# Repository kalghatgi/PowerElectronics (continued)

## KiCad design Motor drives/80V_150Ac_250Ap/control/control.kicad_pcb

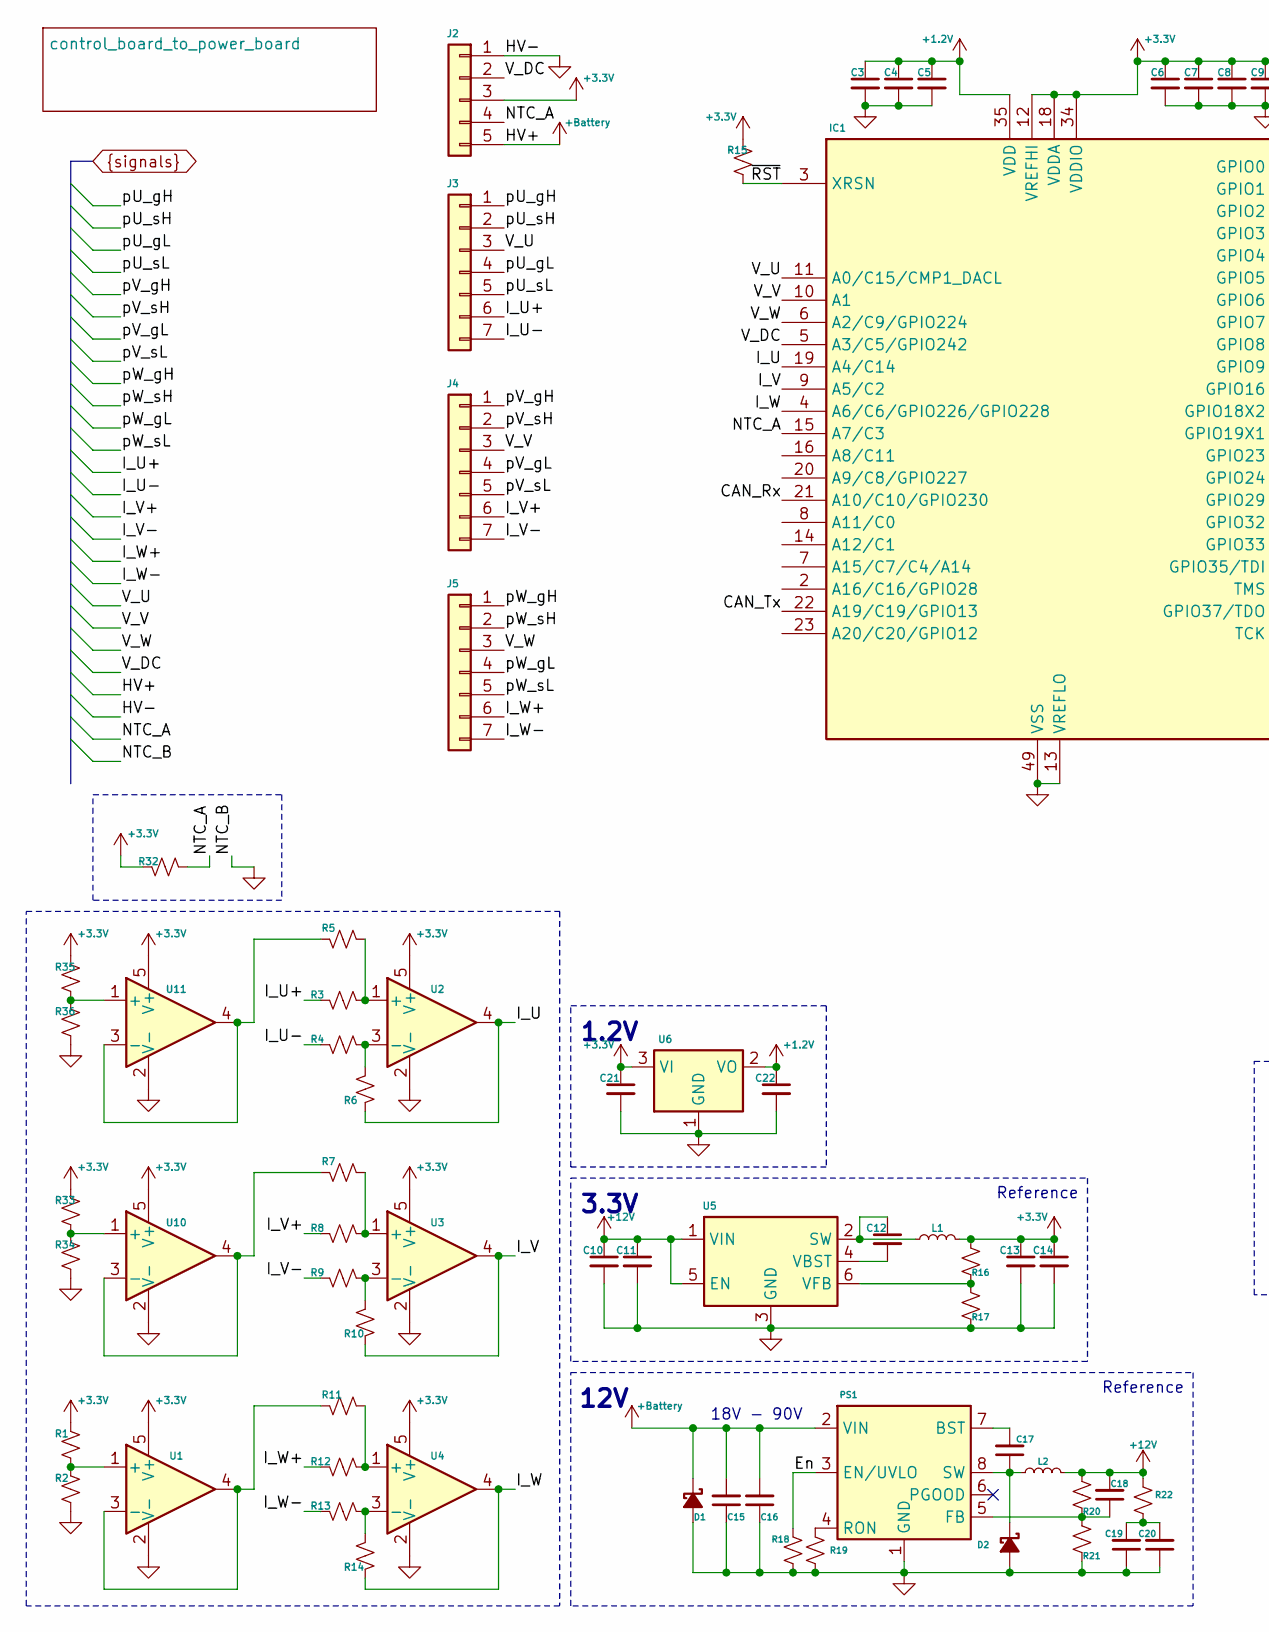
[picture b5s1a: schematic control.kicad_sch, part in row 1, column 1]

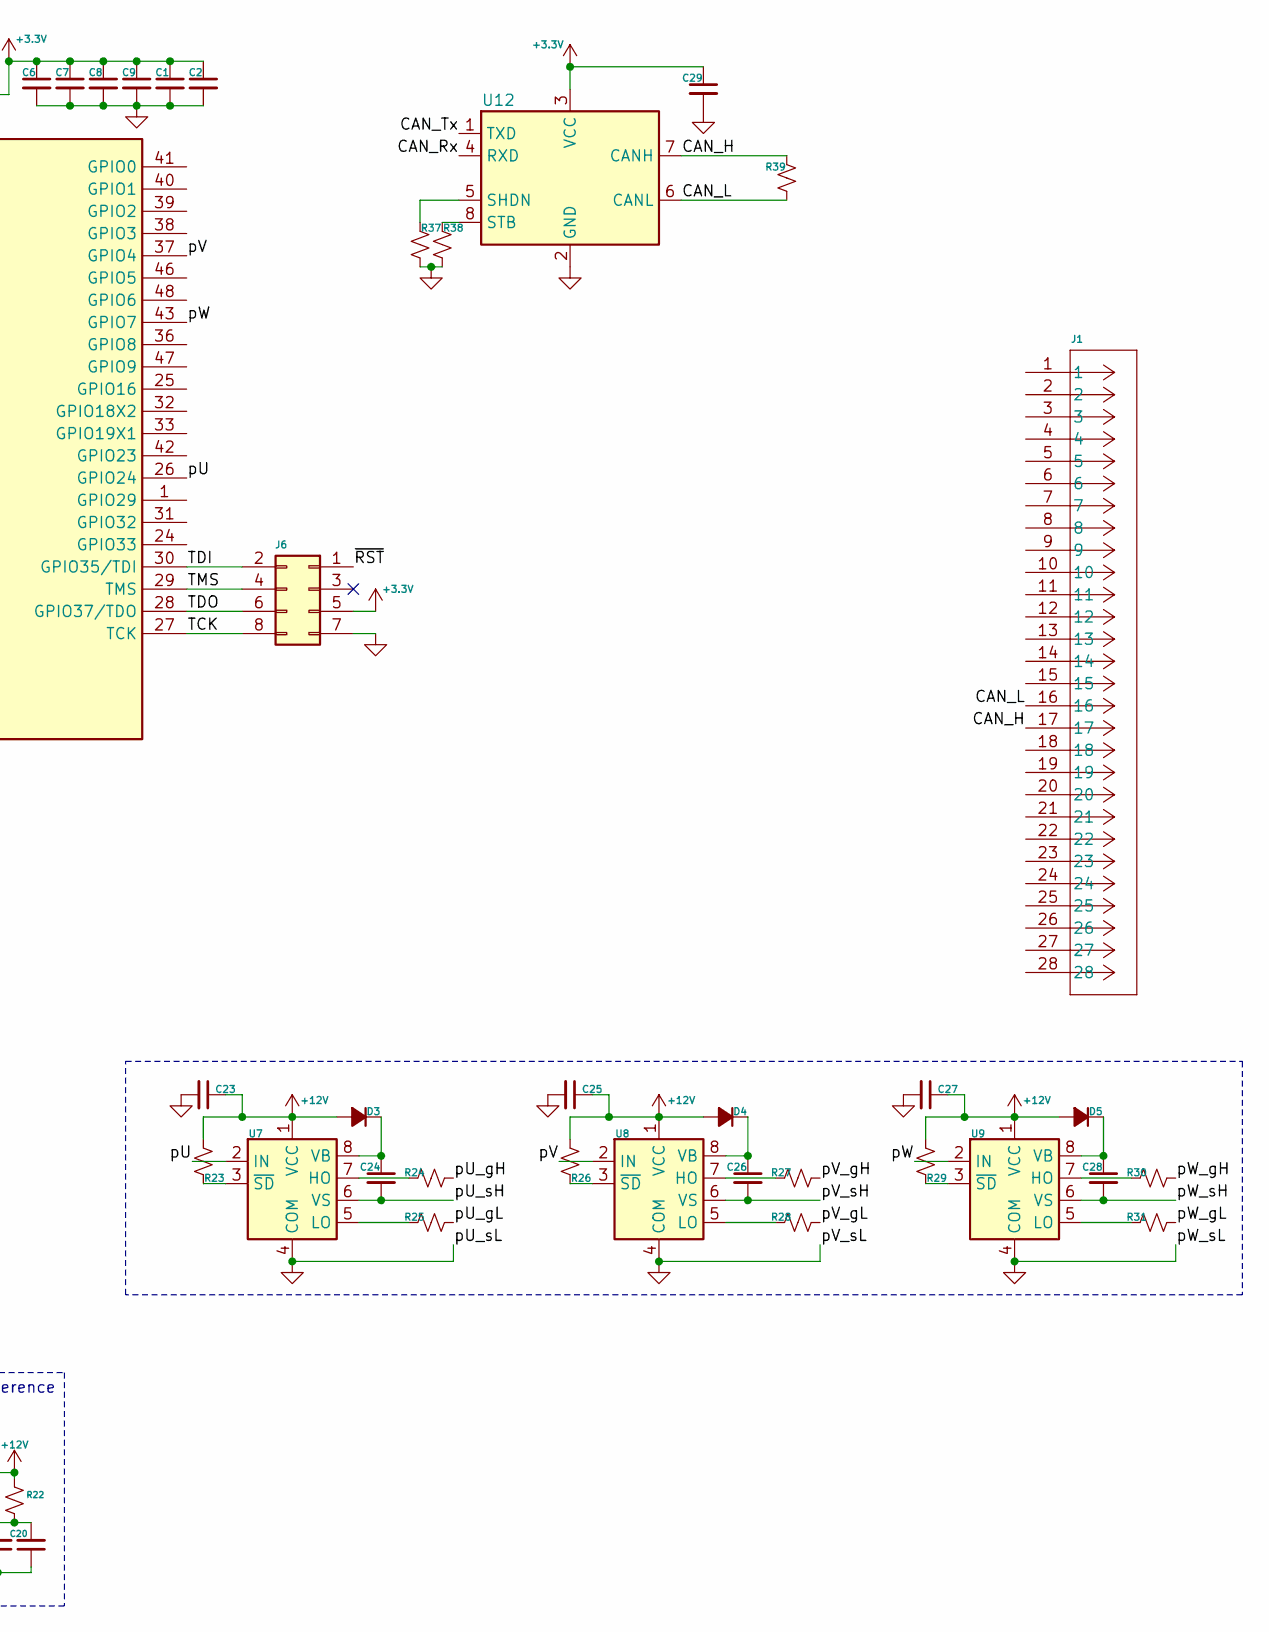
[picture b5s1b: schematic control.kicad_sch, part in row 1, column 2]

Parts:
C1, C6, C7, C8, C9, C21, C29: 1uF, >=6.3V; C_0402_1005Metric
C2, C4: 100nF, >=6.3V; C_0402_1005Metric
C3, C5: 4.7uF, >=6.3V; C_0402_1005Metric
C10, C23, C25, C27: 10uF, >=25V; C_0603_1608Metric
C11, C12: 100nF, >=25V; C_0603_1608Metric
C13, C14: 22uF, >=6.3V; C_0603_1608Metric
C15, C16: 2.2uF, >=100V, 1206; C_1210_3225Metric; MPN mcmt32b225k101ct
C17: 2200pF, >=25V, 0603; C_0603_1608Metric; MPN mc0805b222k500ct
C18: 100pF, >=25V, 0402; C_0402_1005Metric; MPN mc0402b101k500ct
C19, C20: 22uF, >=25V, 0603; C_0603_1608Metric; MPN grm21br61e226me44k
C22: 10uF, >=6.3V; C_0402_1005Metric
C24, C26, C28: 100nF, >=25V; C_1206_3216Metric
D1: Vs=110V Vb=120V SOD-123; D_SOD-123F; MPN pmeg120g10elrx
D2: Vr=100V Vf=0.6V If=2.5A; D_SMP_DO-220AA; MPN v3pm10-m3-h
D3, D4, D5: Vr>=600V, If>=1A; D_SOD-123
IC1: F2800137RGZR; QFN-48-1EP_7x7mm_P0.5mm_EP5.1x5.1mm
J1: 28pin, latch, sealed; 477450100
J2: Conn_01x05; PinHeader_1x05_P2.54mm_Vertical; MPN 7818
J3: Conn_01x07; PinHeader_1x07_P2.54mm_Vertical; MPN 7819
J4: Conn_01x07; PinHeader_1x07_P2.54mm_Vertical; MPN 7820
J5: Conn_01x07; PinHeader_1x07_P2.54mm_Vertical; MPN 7822
J6: Conn_02x04_Counter_Clockwise; PinHeader_2x04_P2.54mm_Vertical
L1: 3.3uH, >=0.5A; L_0805_2012Metric; MPN LQM21PN3R3NGRD
L2: 150uH, <=900mOhm; L_Taiyo-Yuden_MD-4040; MPN 74404054151
PS1: Vin>=90V, Iout>=2.0A; SOIC-8-1EP_3.9x4.9mm_P1.27mm_EP2.29x3mm_ThermalVias; MPN LM5012DDAR
R1, R2, R3, R4, R5, R6, R7, R8, R9, R10, R11, R12, R13, R14, R15, R23, R26, R29, R32, R33, R34, R35, R36, R37, R38: 10K, 62.5mW, 0402; R_0402_1005Metric
R16: 30.9K, >62.5mW, 0402; R_0402_1005Metric
R17: 10K, >62.5mW, 0402; R_0402_1005Metric
R18: 10K, >=62.5mW, 0402; R_0402_1005Metric; MPN mcwr04x1002ftl
R19: 59K, >=62.5mW, 0402; R_0402_1005Metric; MPN mcwr04x5902ftl
R20: 453K, >=62.5mW, 0402; R_0402_1005Metric; MPN mcmr04x4533ftl
R21: 49.9K, >=62.5mW, 0402; R_0402_1005Metric; MPN mcwr04x4992ftl
R22: 0.560R, 62.5mW, 0402; R_0402_1005Metric; MPN rl0402fr-070r5l
R24, R25, R27, R28, R30, R31: 4R, 62.5mW, 0402; R_0402_1005Metric
R39: 120R, 62.5mW, 0402; R_0402_1005Metric
U1, U2, U3, U4, U10, U11: LMV321; SOT-353_SC-70-5
U5: TPS562202; SOT-563
U6: LD1117S12TR_SOT223; SOT-223-3_TabPin2
U7, U8, U9: IR2104; SOIC-8_3.9x4.9mm_P1.27mm
U12: TCAN3414DR; SOIC-8_3.9x4.9mm_P1.27mm

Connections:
+1.2V: C3.1, C4.1, C5.1, C22.1, IC1.35 (VDD), IC1.44 (VDD), U6.2 (VO)
+3.3V: C1.1, C2.1, C6.1, C7.1, C8.1, C9.1, C13.1, C14.1, C21.1, C29.1, IC1.12 (VREFHI), IC1.18 (VDDA), IC1.34 (VDDIO), IC1.45 (VDDIO), J2.3, J6.5, L1.1, R1.1, R15.1, R16.1, R32.2, R33.1, R35.1, U1.5 (V+), U2.5 (V+), U3.5 (V+), U4.5 (V+), U6.3 (VI), U10.5 (V+), U11.5 (V+), U12.3 (VCC)
+12V: C10.1, C11.1, C18.2, C23.1, C25.1, C27.1, D3.2 (A), D4.2 (A), D5.2 (A), L2.2, R20.1, R22.1, R23.1, R26.1, R29.1, U5.1 (VIN), U5.5 (EN), U7.1 (VCC), U8.1 (VCC), U9.1 (VCC)
+Battery: C15.2, C16.2, D1.1 (K), J2.5, PS1.2 (VIN)
/CAN_H: J1.17, R39.1, U12.7 (CANH)
/CAN_L: J1.16, R39.2, U12.6 (CANL)
/CAN_Rx: IC1.21 (A10/C10/GPIO230), U12.4 (RXD)
/CAN_Tx: IC1.22 (A19/C19/GPIO13), U12.1 (TXD)
/En: PS1.3 (EN/UVLO), R18.1
/I_U: IC1.19 (A4/C14), R6.1, U2.4
/I_V: IC1.9 (A5/C2), R10.1, U3.4
/I_W: IC1.4 (A6/C6/GPIO226/GPIO228), R14.1, U4.4
/TCK: IC1.27 (TCK), J6.8
/TDI: IC1.30 (GPIO35/TDI), J6.2
/TDO: IC1.28 (GPIO37/TDO), J6.6
/TMS: IC1.29 (TMS), J6.4
/pU: IC1.26 (GPIO24), U7.2 (IN)
/pV: IC1.37 (GPIO4), U8.2 (IN)
/pW: IC1.43 (GPIO7), U9.2 (IN)
/~RST: IC1.3 (XRSN), J6.1, R15.2
GND0: C1.2, C2.2, C3.2, C4.2, C5.2, C6.2, C7.2, C8.2, C9.2, C10.2, C11.2, C13.2, C14.2, C15.1, C16.1, C19.1, C20.1, C21.2, C22.2, C23.2, C25.2, C27.2, C29.2, D1.2 (A), D2.2 (A), IC1.13 (VREFLO), IC1.17 (VSSA), IC1.49 (VSS), J2.1, J3.5, J4.5, J5.5, J6.7, PS1.1 (GND), PS1.9 (GND_thermal), R2.2, R17.2, R18.2, R19.1, R21.2, R34.2, R36.2, R37.2, R38.2, U1.2 (V-), U2.2 (V-), U3.2 (V-), U4.2 (V-), U5.3 (GND), U6.1 (GND), U7.4 (COM), U8.4 (COM), U9.4 (COM), U10.2 (V-), U11.2 (V-), U12.2 (GND)
I_U+: J3.6, R3.2
I_U-: J3.7, R4.2
I_V+: J4.6, R8.2
I_V-: J4.7, R9.2
I_W+: J5.6, R12.2
I_W-: J5.7, R13.2
NTC_A: IC1.15 (A7/C3), J2.4, R32.1
unnamed: C19.2, C20.2, R22.2
unnamed: C17.1, D2.1 (K), L2.1, PS1.8 (SW)
unnamed: C24.1, D3.1 (K), U7.8 (VB)
unnamed: C26.1, D4.1 (K), U8.8 (VB)
unnamed: C28.1, D5.1 (K), U9.8 (VB)
unnamed: C17.2, PS1.7 (BST)
unnamed: C18.1, PS1.5 (FB), R20.2, R21.1
unnamed: PS1.4 (RON), R19.2
unnamed: R1.2, R2.1, U1.1 (+)
unnamed: R11.2, U1.3 (-), U1.4
unnamed: R3.1, R5.1, U2.1 (+)
unnamed: R4.1, R6.2, U2.3 (-)
unnamed: R7.1, R8.1, U3.1 (+)
unnamed: R9.1, R10.2, U3.3 (-)
unnamed: R11.1, R12.1, U4.1 (+)
unnamed: R13.1, R14.2, U4.3 (-)
unnamed: C12.1, L1.2, U5.2 (SW)
unnamed: C12.2, U5.4 (VBST)
unnamed: R16.2, R17.1, U5.6 (VFB)
unnamed: R24.2, U7.7 (HO)
unnamed: R25.2, U7.5 (LO)
unnamed: R23.2, U7.3 (~SD)
unnamed: R27.2, U8.7 (HO)
unnamed: R28.2, U8.5 (LO)
unnamed: R26.2, U8.3 (~SD)
unnamed: R30.2, U9.7 (HO)
unnamed: R31.2, U9.5 (LO)
unnamed: R29.2, U9.3 (~SD)
unnamed: R33.2, R34.1, U10.1 (+)
unnamed: R7.2, U10.3 (-), U10.4
unnamed: R35.2, R36.1, U11.1 (+)
unnamed: R5.2, U11.3 (-), U11.4
unnamed: R37.1, U12.5 (SHDN)
unnamed: R38.1, U12.8 (STB)
V_DC: IC1.5 (A3/C5/GPIO242), J2.2
V_U: IC1.11 (A0/C15/CMP1_DACL), J3.3
V_V: IC1.10 (A1), J4.3
V_W: IC1.6 (A2/C9/GPIO224), J5.3
pU_gH: J3.1, R24.1
pU_gL: J3.4, R25.1
pU_sH: C24.2, J3.2, U7.6 (VS)
pV_gH: J4.1, R27.1
pV_gL: J4.4, R28.1
pV_sH: C26.2, J4.2, U8.6 (VS)
pW_gH: J5.1, R30.1
pW_gL: J5.4, R31.1
pW_sH: C28.2, J5.2, U9.6 (VS)

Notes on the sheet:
12V
Reference
18V - 90V
3.3V
1.2V

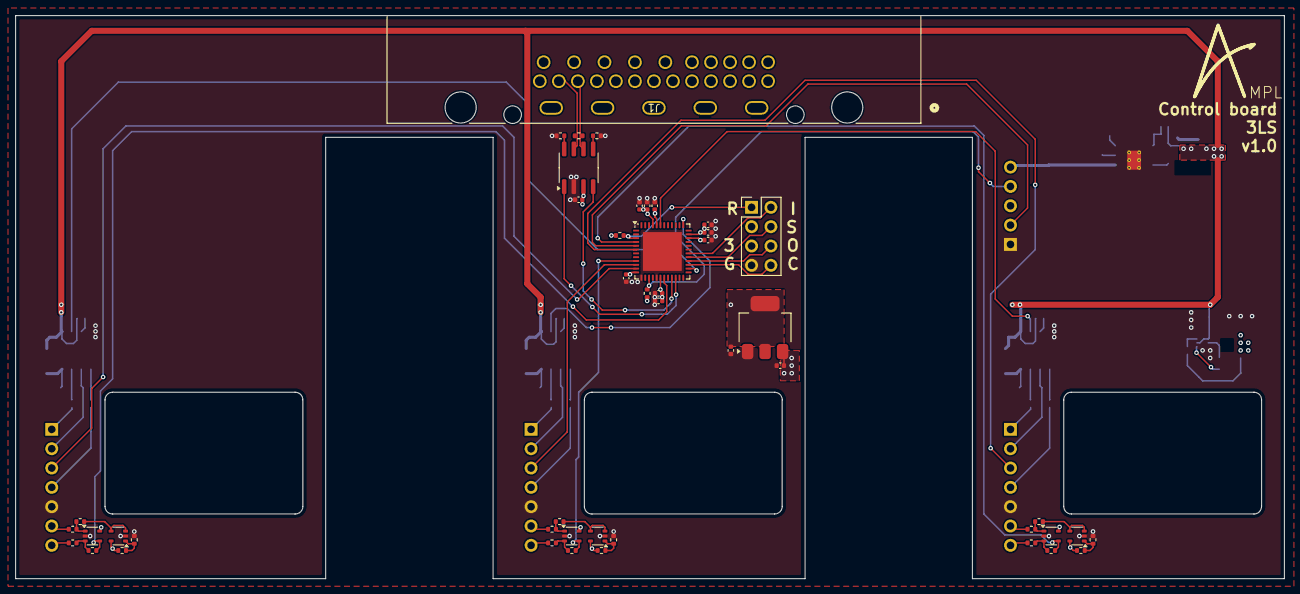
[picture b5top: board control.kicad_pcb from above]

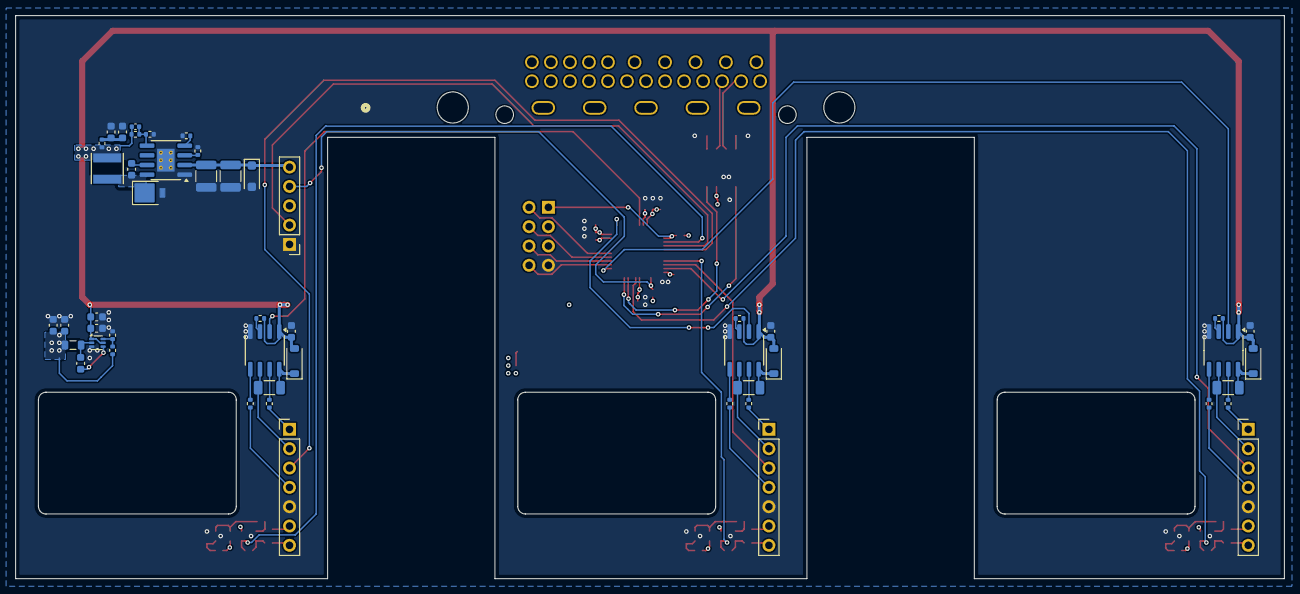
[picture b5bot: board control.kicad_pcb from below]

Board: 4 copper layers, 166.8 x 74.0 mm, 95 parts (49 on the bottom side), 75 nets.

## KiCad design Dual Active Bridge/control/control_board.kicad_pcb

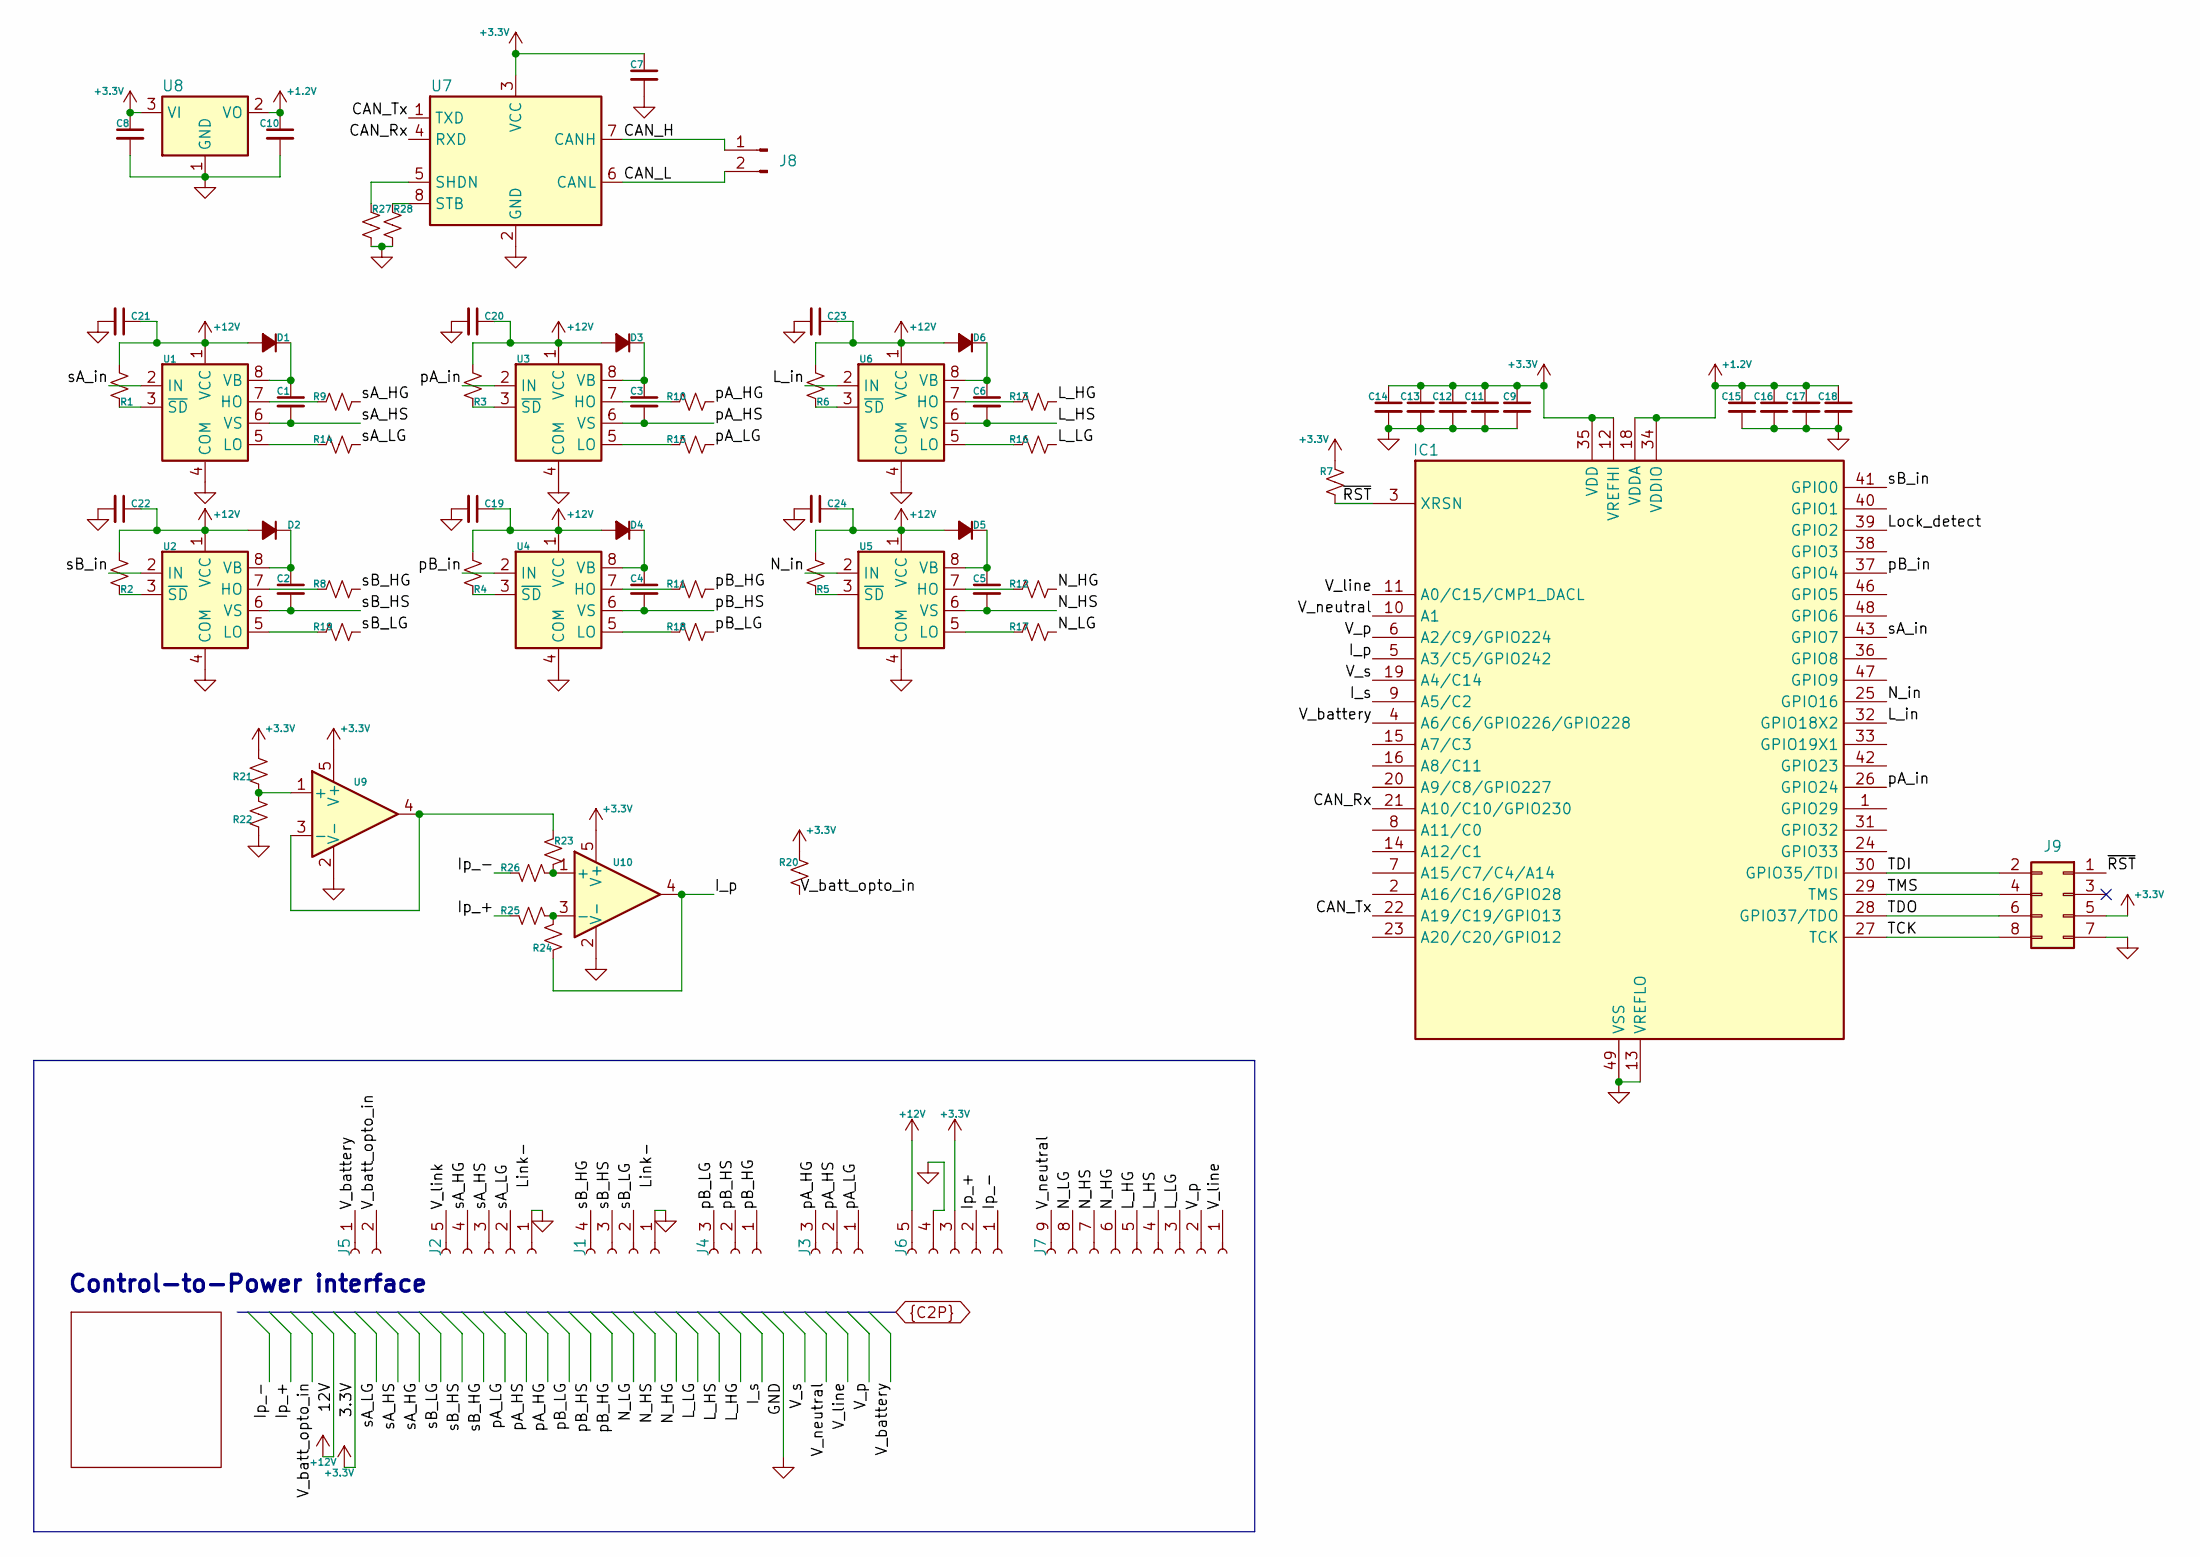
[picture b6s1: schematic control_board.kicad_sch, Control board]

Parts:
C1, C2, C3, C4, C5, C6: 100nF, >=25V; C_1206_3216Metric
C7, C8, C14, C15, C16, C17, C18: 1uF, >=6.3V; C_0402_1005Metric
C9, C10: 10uF, >=6.3V; C_0402_1005Metric
C11, C13: 100nF, >=6.3V; C_0402_1005Metric
C12: 4.7uF, >=6.3V; C_0402_1005Metric
C19, C20, C21, C22, C23, C24: 10uF, >=25V; C_0603_1608Metric
D1, D2, D3, D4, D5, D6: Vr>=600V, If>=1A; D_SOD-123
IC1: F2800137RGZR; QFN-48-1EP_7x7mm_P0.5mm_EP5.1x5.1mm
J1: Conn_01x04_Socket; PinSocket_1x04_P2.54mm_Horizontal
J2, J6: Conn_01x04_Socket; PinSocket_1x05_P2.54mm_Horizontal
J3, J4: Conn_01x04_Socket; PinSocket_1x03_P2.54mm_Horizontal
J5: Conn_01x04_Socket; PinSocket_1x02_P2.54mm_Horizontal
J7: Conn_01x04_Socket; PinSocket_1x09_P2.54mm_Horizontal
J8: Conn_01x02_Pin; JST_PH_S2B-PH-SM4-TB_1x02-1MP_P2.00mm_Horizontal
J9: Conn_02x04_Counter_Clockwise; PinHeader_2x04_P2.54mm_Vertical
R1, R2, R3, R4, R5, R6, R7, R20, R21, R22, R23, R24, R25, R26, R27, R28: 10K, 62.5mW, 0402; R_0402_1005Metric
R8, R9, R10, R11, R12, R13, R14, R15, R16, R17, R18, R19: 4R, 62.5mW, 0402; R_0402_1005Metric
U1, U2, U3, U4, U5, U6: IR2104; SOIC-8_3.9x4.9mm_P1.27mm
U7: TCAN3414DR; SOIC-8_3.9x4.9mm_P1.27mm
U8: LD1117S12TR_SOT223; SOT-223-3_TabPin2
U9, U10: LMV321; SOT-353_SC-70-5

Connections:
+1.2V: C10.1, C15.1, C16.1, C17.1, C18.1, IC1.18 (VDDA), IC1.34 (VDDIO), IC1.45 (VDDIO), U8.2 (VO)
+3.3V: C7.1, C8.1, C9.1, C11.1, C12.1, C13.1, C14.1, IC1.12 (VREFHI), IC1.35 (VDD), IC1.44 (VDD), J6.3, J9.5, R7.1, R20.1, R21.1, U7.3 (VCC), U8.3 (VI), U9.5 (V+), U10.5 (V+)
+12V: C19.1, C20.1, C21.1, C22.1, C23.1, C24.1, D1.2 (A), D2.2 (A), D3.2 (A), D4.2 (A), D5.2 (A), D6.2 (A), J6.5, R1.1, R2.1, R3.1, R4.1, R5.1, R6.1, U1.1 (VCC), U2.1 (VCC), U3.1 (VCC), U4.1 (VCC), U5.1 (VCC), U6.1 (VCC)
/CAN_H: J8.1, U7.7 (CANH)
/CAN_L: J8.2, U7.6 (CANL)
/CAN_Rx: IC1.21 (A10/C10/GPIO230), U7.4 (RXD)
/CAN_Tx: IC1.22 (A19/C19/GPIO13), U7.1 (TXD)
/I_p: IC1.5 (A3/C5/GPIO242), R24.1, U10.4
/I_s: IC1.9 (A5/C2)
/Ip_+: J6.2, R25.2
/Ip_-: J6.1, R26.2
/L_HG: J7.5, R13.1
/L_HS: C6.2, J7.4, U6.6 (VS)
/L_LG: J7.3, R16.1
/L_in: IC1.32 (GPIO18X2), U6.2 (IN)
/Lock_detect: IC1.39 (GPIO2)
/N_HG: J7.6, R12.1
/N_HS: C5.2, J7.7, U5.6 (VS)
/N_LG: J7.8, R17.1
/N_in: IC1.25 (GPIO16), U5.2 (IN)
/TCK: IC1.27 (TCK), J9.8
/TDI: IC1.30 (GPIO35/TDI), J9.2
/TDO: IC1.28 (GPIO37/TDO), J9.6
/TMS: IC1.29 (TMS), J9.4
/V_batt_opto_in: J5.2, R20.2
/V_battery: IC1.4 (A6/C6/GPIO226/GPIO228), J5.1
/V_line: IC1.11 (A0/C15/CMP1_DACL), J7.1
/V_link: J2.5
/V_neutral: IC1.10 (A1), J7.9
/V_p: IC1.6 (A2/C9/GPIO224), J7.2
/V_s: IC1.19 (A4/C14)
/pA_in: IC1.26 (GPIO24), U3.2 (IN)
/pB_in: IC1.37 (GPIO4), U4.2 (IN)
/sA_in: IC1.43 (GPIO7), U1.2 (IN)
/sB_in: IC1.41 (GPIO0), U2.2 (IN)
/~RST: IC1.3 (XRSN), J9.1, R7.2
GND0: C7.2, C8.2, C9.2, C10.2, C11.2, C12.2, C13.2, C14.2, C15.2, C16.2, C17.2, C18.2, C19.2, C20.2, C21.2, C22.2, C23.2, C24.2, IC1.13 (VREFLO), IC1.17 (VSSA), IC1.49 (VSS), J1.1, J2.1, J6.4, J9.7, R22.2, R27.2, R28.2, U1.4 (COM), U2.4 (COM), U3.4 (COM), U4.4 (COM), U5.4 (COM), U6.4 (COM), U7.2 (GND), U8.1 (GND), U9.2 (V-), U10.2 (V-)
unnamed: C1.1, D1.1 (K), U1.8 (VB)
unnamed: C2.1, D2.1 (K), U2.8 (VB)
unnamed: C3.1, D3.1 (K), U3.8 (VB)
unnamed: C4.1, D4.1 (K), U4.8 (VB)
unnamed: C5.1, D5.1 (K), U5.8 (VB)
unnamed: C6.1, D6.1 (K), U6.8 (VB)
unnamed: R9.2, U1.7 (HO)
unnamed: R14.2, U1.5 (LO)
unnamed: R1.2, U1.3 (~SD)
unnamed: R8.2, U2.7 (HO)
unnamed: R19.2, U2.5 (LO)
unnamed: R2.2, U2.3 (~SD)
unnamed: R10.2, U3.7 (HO)
unnamed: R15.2, U3.5 (LO)
unnamed: R3.2, U3.3 (~SD)
unnamed: R11.2, U4.7 (HO)
unnamed: R18.2, U4.5 (LO)
unnamed: R4.2, U4.3 (~SD)
unnamed: R12.2, U5.7 (HO)
unnamed: R17.2, U5.5 (LO)
unnamed: R5.2, U5.3 (~SD)
unnamed: R13.2, U6.7 (HO)
unnamed: R16.2, U6.5 (LO)
unnamed: R6.2, U6.3 (~SD)
unnamed: R27.1, U7.5 (SHDN)
unnamed: R28.1, U7.8 (STB)
unnamed: R21.2, R22.1, U9.1 (+)
unnamed: R23.2, U9.3 (-), U9.4
unnamed: R23.1, R26.1, U10.1 (+)
unnamed: R24.2, R25.1, U10.3 (-)
pA_HG: J3.3, R10.1
pA_HS: C3.2, J3.2, U3.6 (VS)
pA_LG: J3.1, R15.1
pB_HG: J4.1, R11.1
pB_HS: C4.2, J4.2, U4.6 (VS)
pB_LG: J4.3, R18.1
sA_HG: J2.4, R9.1
sA_HS: C1.2, J2.3, U1.6 (VS)
sA_LG: J2.2, R14.1
sB_HG: J1.4, R8.1
sB_HS: C2.2, J1.3, U2.6 (VS)
sB_LG: J1.2, R19.1

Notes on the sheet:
Control-to-Power interface

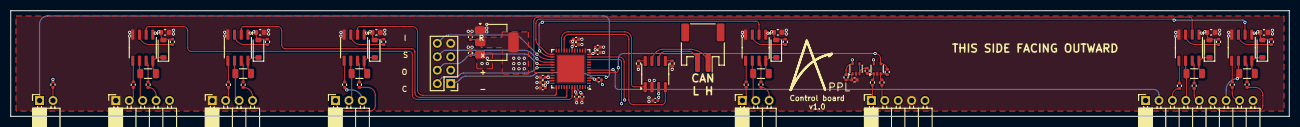
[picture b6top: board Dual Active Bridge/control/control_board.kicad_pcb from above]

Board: 4 copper layers, 242.0 x 20.0 mm, 78 parts (0 on the bottom side), 75 nets.

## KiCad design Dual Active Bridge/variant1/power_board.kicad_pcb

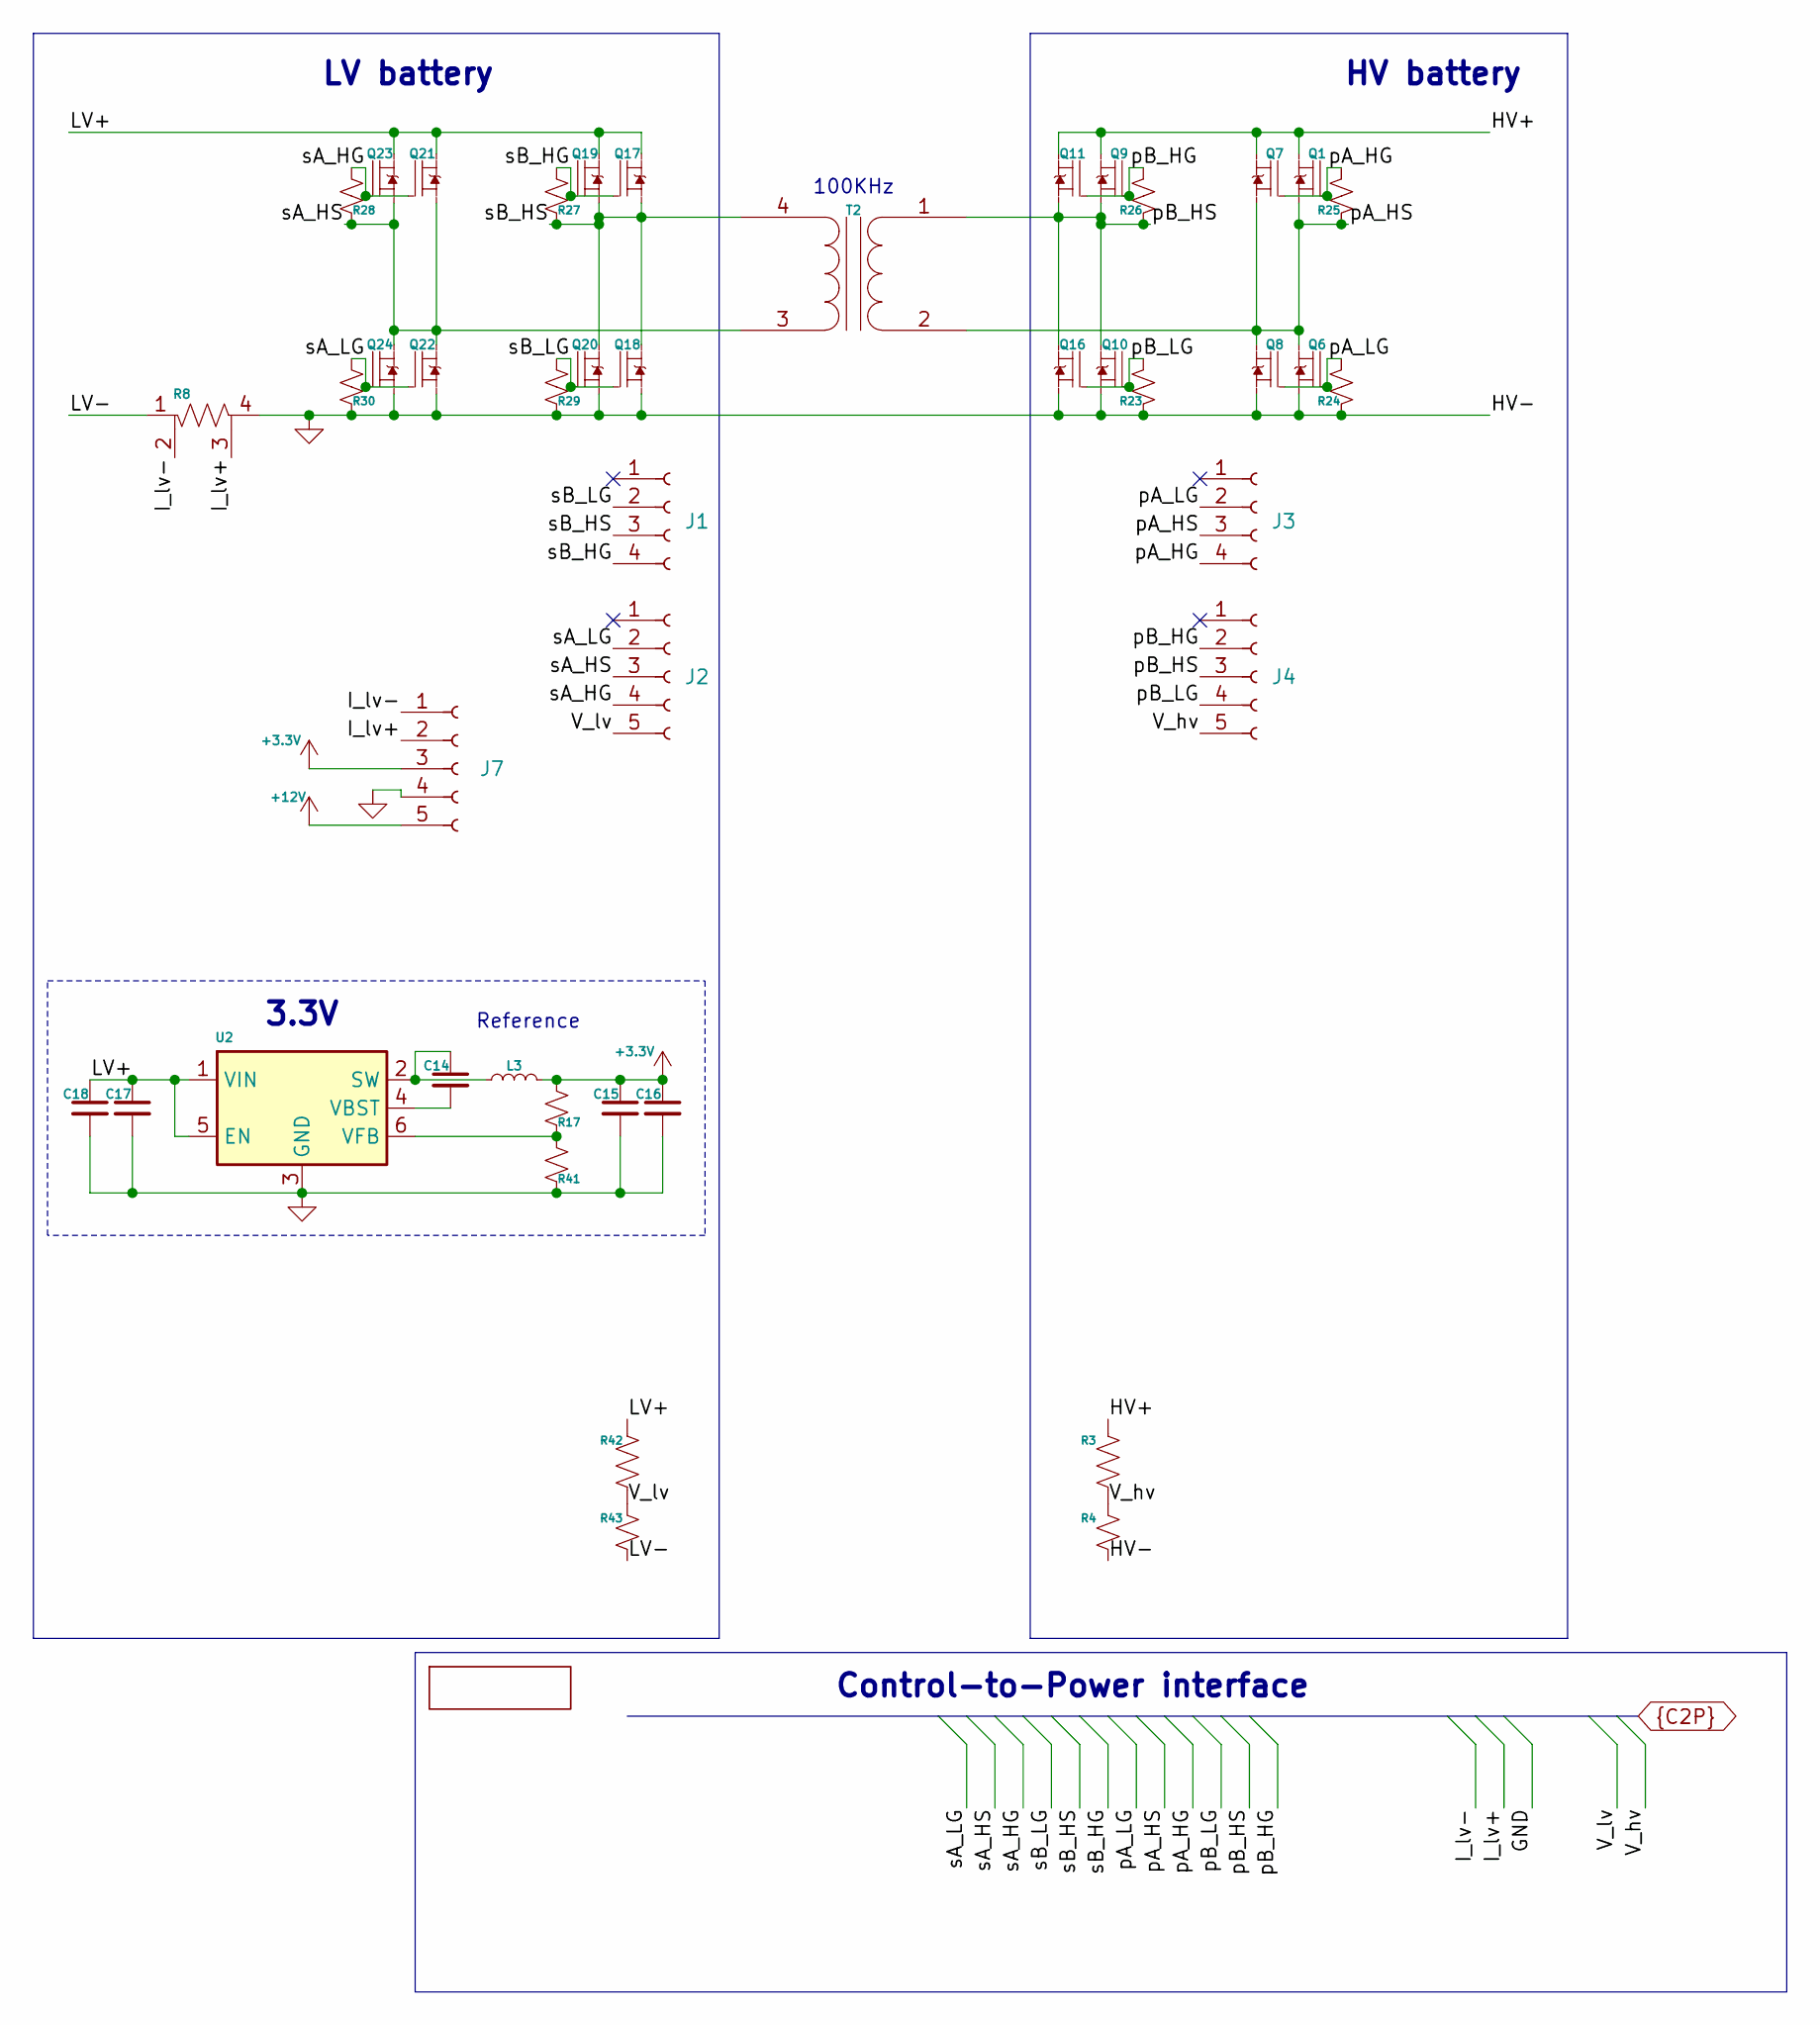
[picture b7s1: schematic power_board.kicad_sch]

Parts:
C14, C17: 100nF, >=25V; C_0603_1608Metric
C15, C16: 22uF, >=6.3V; C_0603_1608Metric
C18: 10uF, >=25V; C_0603_1608Metric
J1, J3: Conn_01x04_Header; PinHeader_1x04_P2.54mm_Vertical
J2, J4, J7: Conn_01x05_Header; PinHeader_1x05_P2.54mm_Vertical
L3: 3.3uH, >=0.5A; L_0805_2012Metric; MPN LQM21PN3R3NGRD
Q1, Q6, Q7, Q8, Q9, Q10, Q11, Q16: NMOS, Vds>=70V, Rds<=1.5mOhm; IAUCN08S7N013ATMA1; MPN IAUCN08S7N013ATMA1
Q17, Q18, Q19, Q20, Q21, Q22, Q23, Q24: NMOS, Vds>=20V, Rds<=0.5mOhm; IQDH29NE2LM5CGATMA1; MPN IQDH29NE2LM5CGATMA1
R3, R42: 1MOhm, >200V, <1%, >62.5mW; R_1206_3216Metric
R4, R43: 10K, >62.5mW; R_0603_1608Metric
R8: 10mOhm, >=3W; R_shunt_2512_6332Metric; MPN CRA2512-FZ-R010ELF
R17: 30.9K, >62.5mW, 0402; R_0402_1005Metric
R23, R24, R25, R26, R27, R28, R29, R30, R41: 10K, >62.5mW, 0402; R_0402_1005Metric
T2: Np:Ns=5:1, Lk>5.7uH, N87, Isec_RMS=300A
U2: TPS562202; SOT-563

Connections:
+3.3V: C15.1, C16.1, J7.3, L3.1, R17.1
+12V: J7.5
/HV+: Q1.3 (D), Q7.3 (D), Q9.3 (D), Q11.3 (D), R3.1
/LV+: C17.1, C18.1, Q17.5 (D), Q19.5 (D), Q21.5 (D), Q23.5 (D), R42.1, U2.1 (VIN), U2.5 (EN)
/LV-: R8.1, R43.2
GND0: C15.2, C16.2, C17.2, C18.2, J7.4, Q6.2 (S), Q8.2 (S), Q10.2 (S), Q16.2 (S), Q18.2 (S), Q18.3 (S), Q18.4 (S), Q20.2 (S), Q20.3 (S), Q20.4 (S), Q22.2 (S), Q22.3 (S), Q22.4 (S), Q24.2 (S), Q24.3 (S), Q24.4 (S), R4.2, R8.4, R23.2, R24.2, R29.2, R30.2, R41.2, U2.3 (GND)
I_lv+: J7.2, R8.3
I_lv-: J7.1, R8.2
unnamed: C14.1, L3.2, U2.2 (SW)
unnamed: C14.2, U2.4 (VBST)
unnamed: R17.2, R41.1, U2.6 (VFB)
V_hv: J4.5, R3.2, R4.1
V_lv: J2.5, R42.2, R43.1
pA_HG: J3.4, Q1.1 (G), Q7.1 (G), R25.1
pA_HS: J3.3, Q1.2 (S), Q6.3 (D), Q7.2 (S), Q8.3 (D), R25.2, T2.2 (AB)
pA_LG: J3.2, Q6.1 (G), Q8.1 (G), R24.1
pB_HG: J4.2, Q9.1 (G), Q11.1 (G), R26.1
pB_HS: J4.3, Q9.2 (S), Q10.3 (D), Q11.2 (S), Q16.3 (D), R26.2, T2.1 (AA)
pB_LG: J4.4, Q10.1 (G), Q16.1 (G), R23.1
sA_HG: J2.4, Q21.1 (G), Q23.1 (G), R28.1
sA_HS: J2.3, Q21.2 (S), Q21.3 (S), Q21.4 (S), Q22.5 (D), Q23.2 (S), Q23.3 (S), Q23.4 (S), Q24.5 (D), R28.2, T2.3 (SA)
sA_LG: J2.2, Q22.1 (G), Q24.1 (G), R30.1
sB_HG: J1.4, Q17.1 (G), Q19.1 (G), R27.1
sB_HS: J1.3, Q17.2 (S), Q17.3 (S), Q17.4 (S), Q18.5 (D), Q19.2 (S), Q19.3 (S), Q19.4 (S), Q20.5 (D), R27.2, T2.4 (SB)
sB_LG: J1.2, Q18.1 (G), Q20.1 (G), R29.1

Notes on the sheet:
Reference
HV battery
LV battery
Control-to-Power interface
100KHz
3.3V

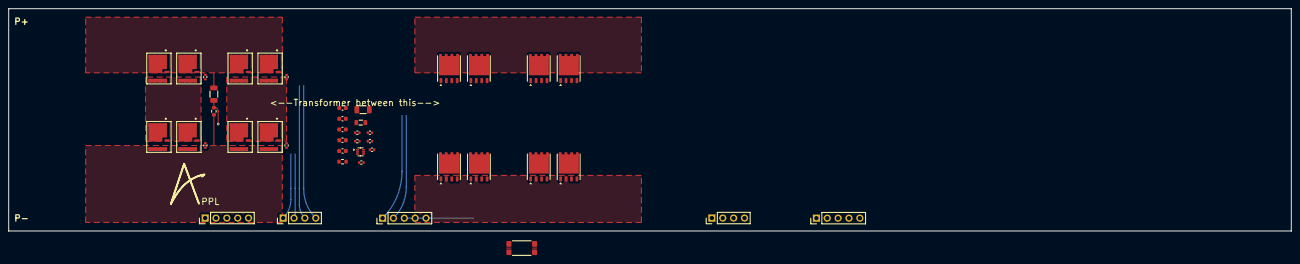
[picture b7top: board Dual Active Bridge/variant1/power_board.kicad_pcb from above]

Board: 2 copper layers, 300.0 x 52.0 mm, 43 parts (0 on the bottom side), 24 nets.

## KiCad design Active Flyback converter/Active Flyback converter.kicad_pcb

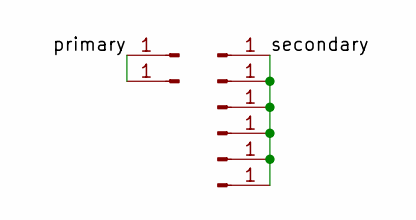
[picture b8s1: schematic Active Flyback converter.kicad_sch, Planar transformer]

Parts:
J1, J2, J3, J4, J5, J6, J7, J8: Conn_01x01_Pin; PinHeader_1x01_P2.54mm_Vertical

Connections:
/primary: J1.1, J3.1
/secondary: J2.1, J4.1, J5.1, J6.1, J7.1, J8.1
